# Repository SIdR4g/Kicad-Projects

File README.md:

# Kicad-Projects
A collection of PCB designs, I built during the course of learning

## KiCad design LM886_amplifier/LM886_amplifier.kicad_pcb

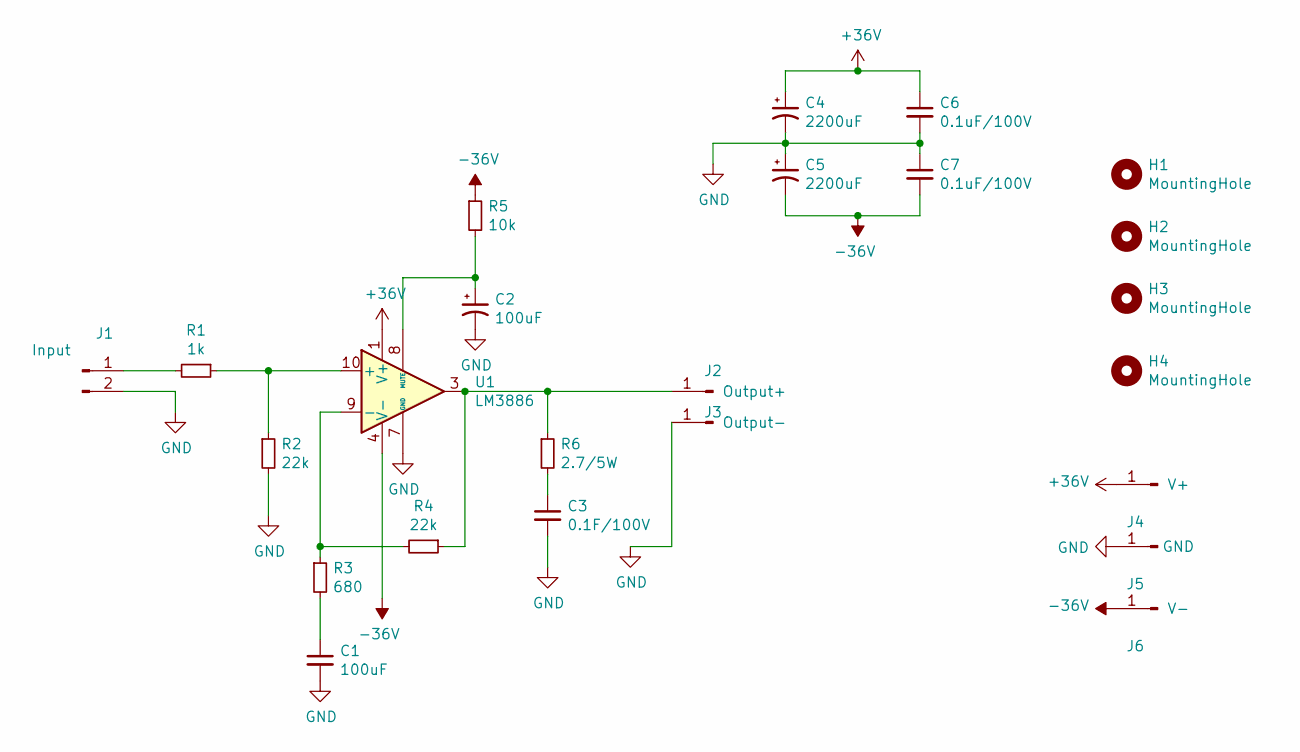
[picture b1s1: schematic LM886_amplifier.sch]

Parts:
C1, C2: 100uF; CP_Radial_D10.0mm_P2.50mm
C3: 0.1F/100V; C_Rect_L7.0mm_W2.0mm_P5.00mm
C4, C5: 2200uF; CP_Radial_D10.0mm_P2.50mm
C6, C7: 0.1uF/100V; C_Rect_L7.0mm_W2.0mm_P5.00mm
H1, H2, H3, H4: MountingHole; MountingHole_3mm_Pad_Via
J1: Input; PinHeader_1x02_P2.54mm_Vertical
J2: Output+; PinHeader_1x2_P2.5mm_Drill1.1mm
J3: Output-; PinHeader_1x2_P2.5mm_Drill1.1mm
J4: V+; PinHeader_1x2_P2.5mm_Drill1.1mm
J5: GND; PinHeader_1x2_P2.5mm_Drill1.1mm
J6: V-; PinHeader_1x2_P2.5mm_Drill1.1mm
R1: 1k; R_2010_5025Metric_Pad1.40x2.65mm_HandSolder
R2, R4: 22k; R_2010_5025Metric_Pad1.40x2.65mm_HandSolder
R3: 680; R_2010_5025Metric_Pad1.40x2.65mm_HandSolder
R5: 10k; R_2010_5025Metric_Pad1.40x2.65mm_HandSolder
R6: 2.7/5W; R_Axial_DIN0207_L6.3mm_D2.5mm_P15.24mm_Horizontal
U1: LM3886; TO-220-11_P3.4x5.08mm_StaggerOdd_Lead4.85mm_Vertical

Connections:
+36V: C4.1, C6.1, J4.1, U1.1 (V+), U1.5 (V+)
-36V: C5.2, C7.2, J6.1, R5.1, U1.4 (V-)
GND: C1.2, C2.2, C3.2, C4.2, C5.1, C6.2, C7.1, J1.2, J3.1, J5.1, R2.2, U1.7 (GND)
unnamed: C1.1, R3.2
unnamed: C2.1, R5.2, U1.8 (MUTE)
unnamed: C3.1, R6.2
unnamed: J1.1, R1.2
unnamed: J2.1, R4.1, R6.1, U1.3
unnamed: R1.1, R2.1, U1.10 (+)
unnamed: R3.1, R4.2, U1.9 (-)

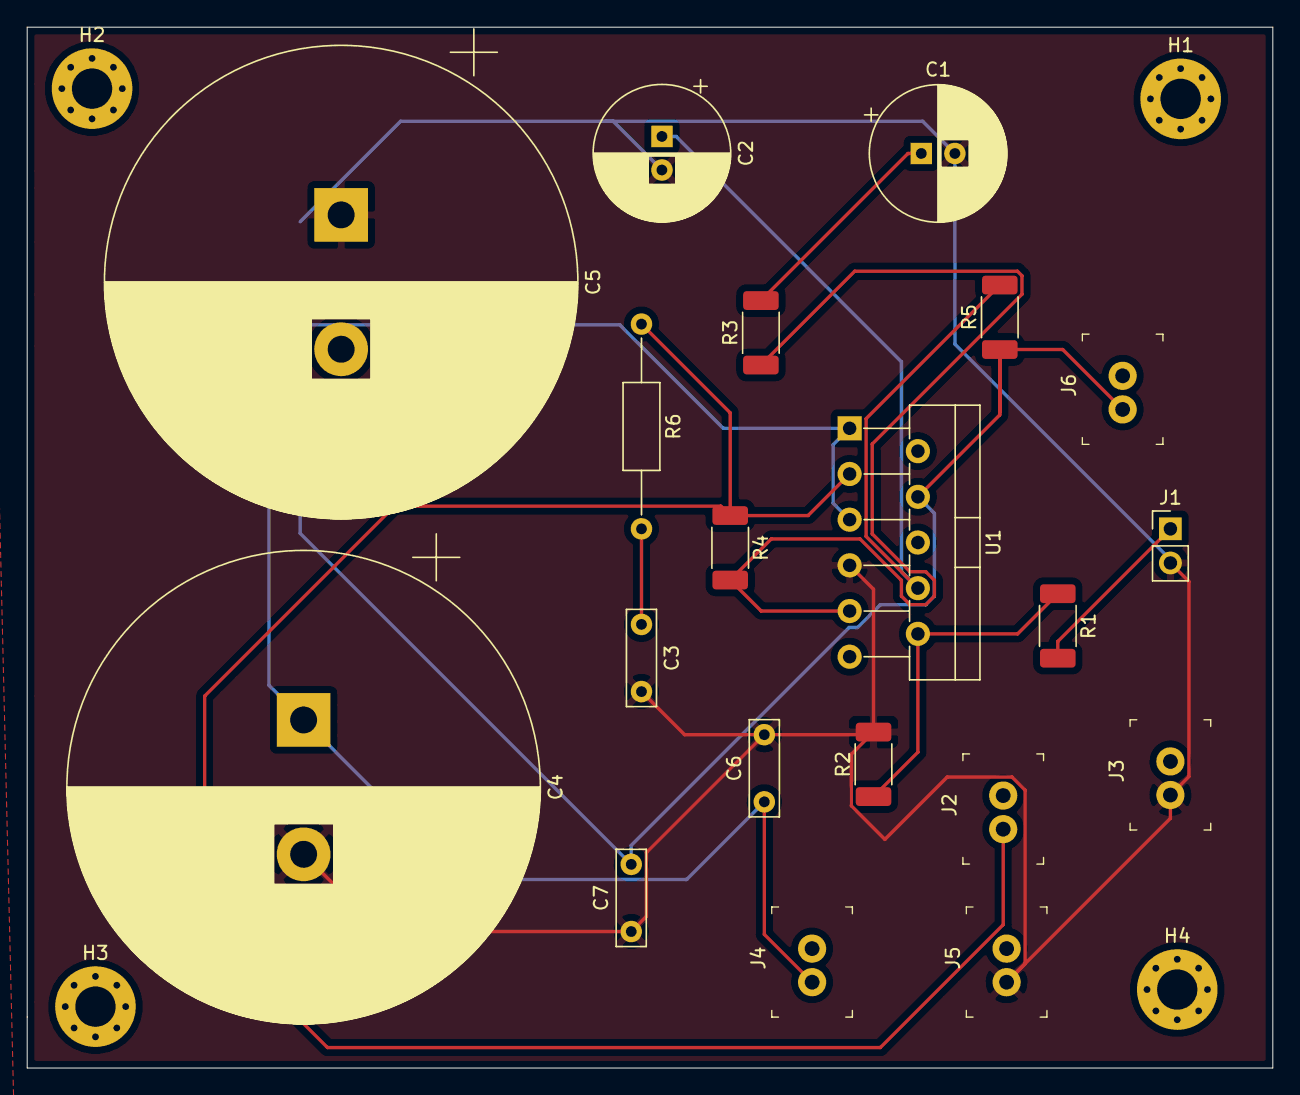
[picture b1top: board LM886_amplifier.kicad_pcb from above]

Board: 2 copper layers, 92.7 x 77.5 mm, 24 parts (0 on the bottom side), 10 nets.

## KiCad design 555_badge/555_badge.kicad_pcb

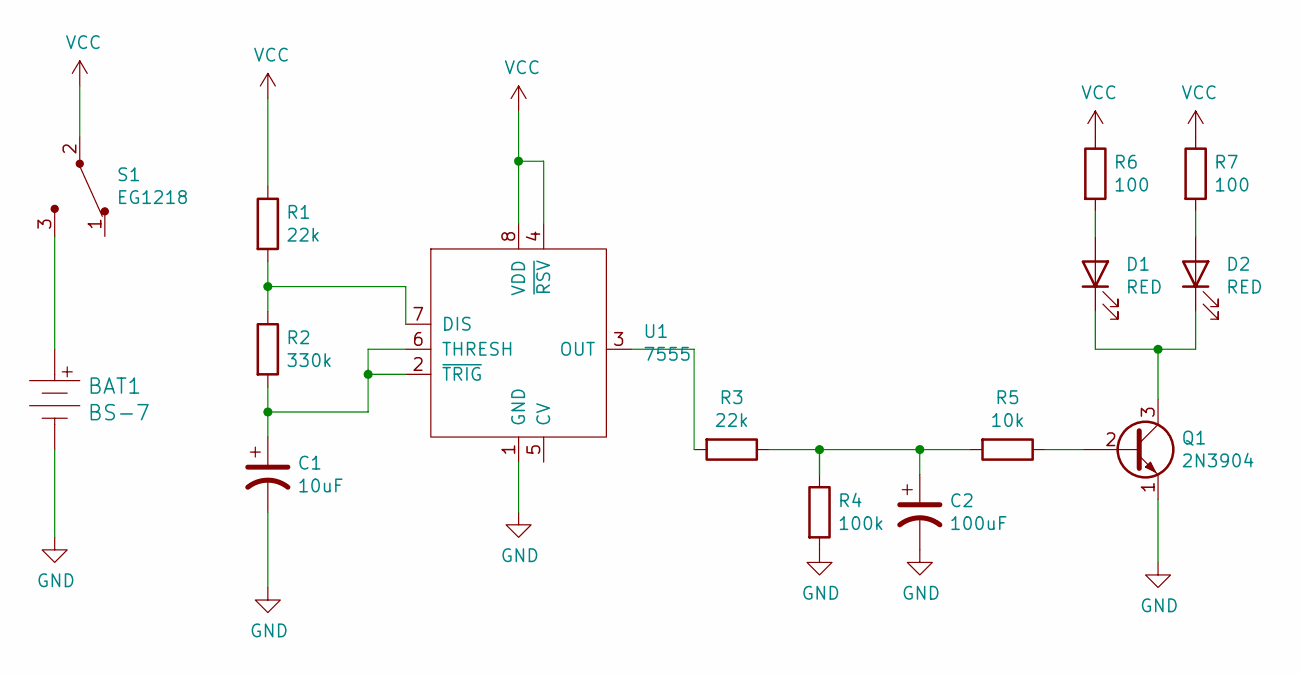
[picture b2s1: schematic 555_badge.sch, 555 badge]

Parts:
BAT1: BS-7; Battery_Holder_Coin_2032_BS-7; MPN BS-7; Digi-Key_PN BS-7-ND
C1: 10uF; CP_Radial_D5.0mm_P2.00mm
C2: 100uF; CP_Radial_D6.3mm_P2.50mm
D1, D2: RED; LED_D3.0mm
Q1: 2N3904; TO-92-3
R1, R3: 22k; R_Axial_DIN0204_L3.6mm_D1.6mm_P7.62mm_Horizontal
R2: 330k; R_Axial_DIN0204_L3.6mm_D1.6mm_P7.62mm_Horizontal
R4: 100k; R_Axial_DIN0204_L3.6mm_D1.6mm_P7.62mm_Horizontal
R5: 10k; R_Axial_DIN0204_L3.6mm_D1.6mm_P7.62mm_Horizontal
R6, R7: 100; R_Axial_DIN0204_L3.6mm_D1.6mm_P7.62mm_Horizontal
S1: EG1218; Switch_Slide_11.6x4mm_EG1218; MPN EG1218; Digi-Key_PN EG1903-ND
U1: 7555; ICM7555-PDIP

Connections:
GND: BAT1.Neg, C1.2, C2.2, Q1.1 (E), R4.2, U1.1 (GND)
unnamed: BAT1.Pos, S1.3
unnamed: C1.1, R2.2, U1.2 (~TRIG), U1.6 (THRESH)
unnamed: C2.1, R3.1, R4.1, R5.2
unnamed: D1.1 (K), D2.1 (K), Q1.3 (C)
unnamed: D1.2 (A), R6.2
unnamed: D2.2 (A), R7.2
unnamed: Q1.2 (B), R5.1
unnamed: R1.2, R2.1, U1.7 (DIS)
unnamed: R3.2, U1.3 (OUT)
VCC: R1.1, R6.1, R7.1, S1.2, U1.4 (~RSV), U1.8 (VDD)

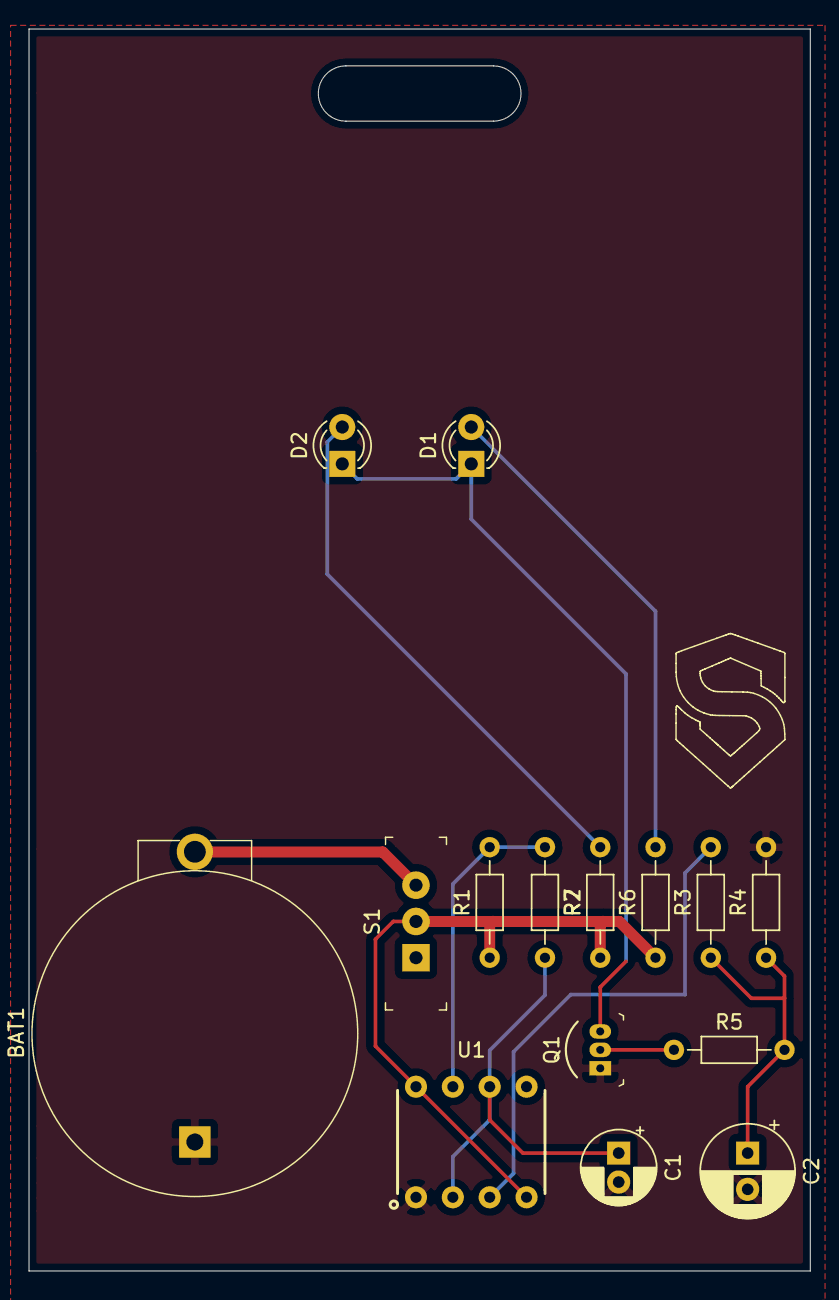
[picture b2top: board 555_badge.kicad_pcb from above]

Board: 2 copper layers, 53.8 x 85.6 mm, 15 parts (0 on the bottom side), 11 nets.

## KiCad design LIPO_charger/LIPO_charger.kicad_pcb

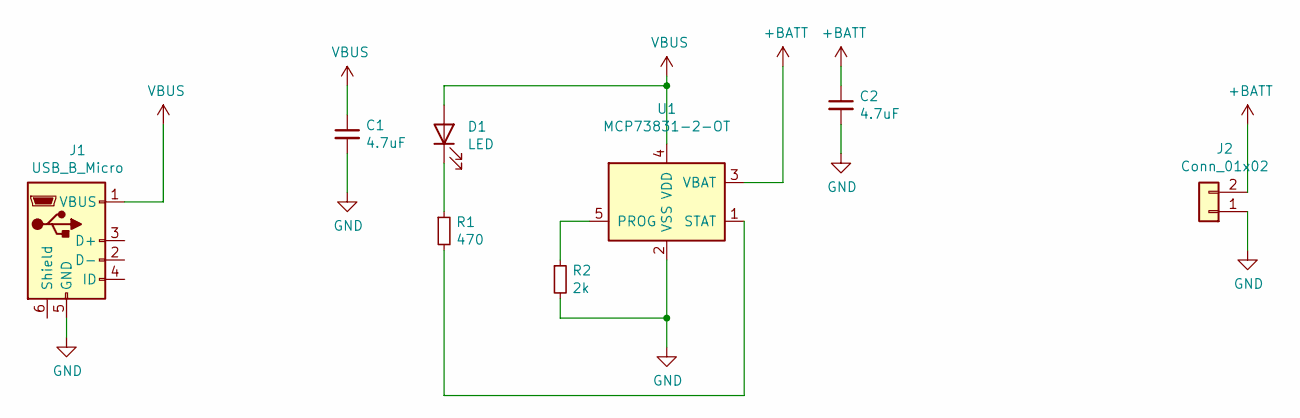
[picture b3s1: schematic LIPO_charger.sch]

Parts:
C1, C2: 4.7uF; C_1210_3225Metric_Pad1.33x2.70mm_HandSolder
D1: LED; LED_1210_3225Metric_Pad1.42x2.65mm_HandSolder
J1: USB_B_Micro; USB_Micro-B_Molex-105017-0001
J2: Conn_01x02; JST_GH_BM02B-GHS-TBT_1x02-1MP_P1.25mm_Vertical
R1: 470; R_1210_3225Metric_Pad1.30x2.65mm_HandSolder
R2: 2k; R_1210_3225Metric_Pad1.30x2.65mm_HandSolder
U1: MCP73831-2-OT; SOT-23-5

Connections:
+BATT: C2.1, J2.2, U1.3 (VBAT)
GND: C1.2, C2.2, J1.5 (GND), J2.1, R2.2, U1.2 (VSS)
unnamed: D1.1 (K), R1.1
unnamed: R1.2, U1.1 (STAT)
unnamed: R2.1, U1.5 (PROG)
VBUS: C1.1, D1.2 (A), J1.1 (VBUS), U1.4 (VDD)

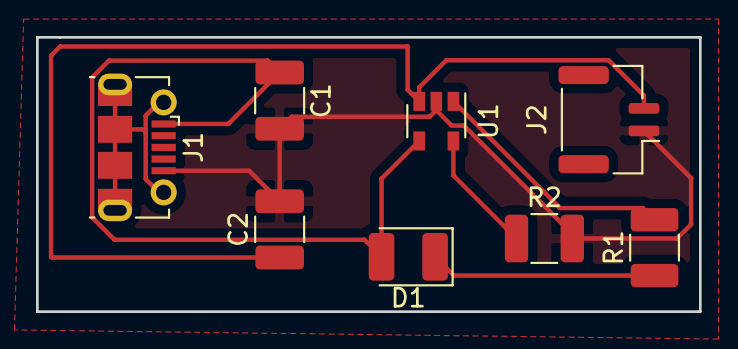
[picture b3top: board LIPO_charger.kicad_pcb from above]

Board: 2 copper layers, 36.8 x 15.2 mm, 8 parts (0 on the bottom side), 6 nets.

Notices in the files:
555_badge/555_badge.sch:
License CC by 4.0
